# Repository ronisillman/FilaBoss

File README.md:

# FilaBoss
Mechatronics Project Filament Maker

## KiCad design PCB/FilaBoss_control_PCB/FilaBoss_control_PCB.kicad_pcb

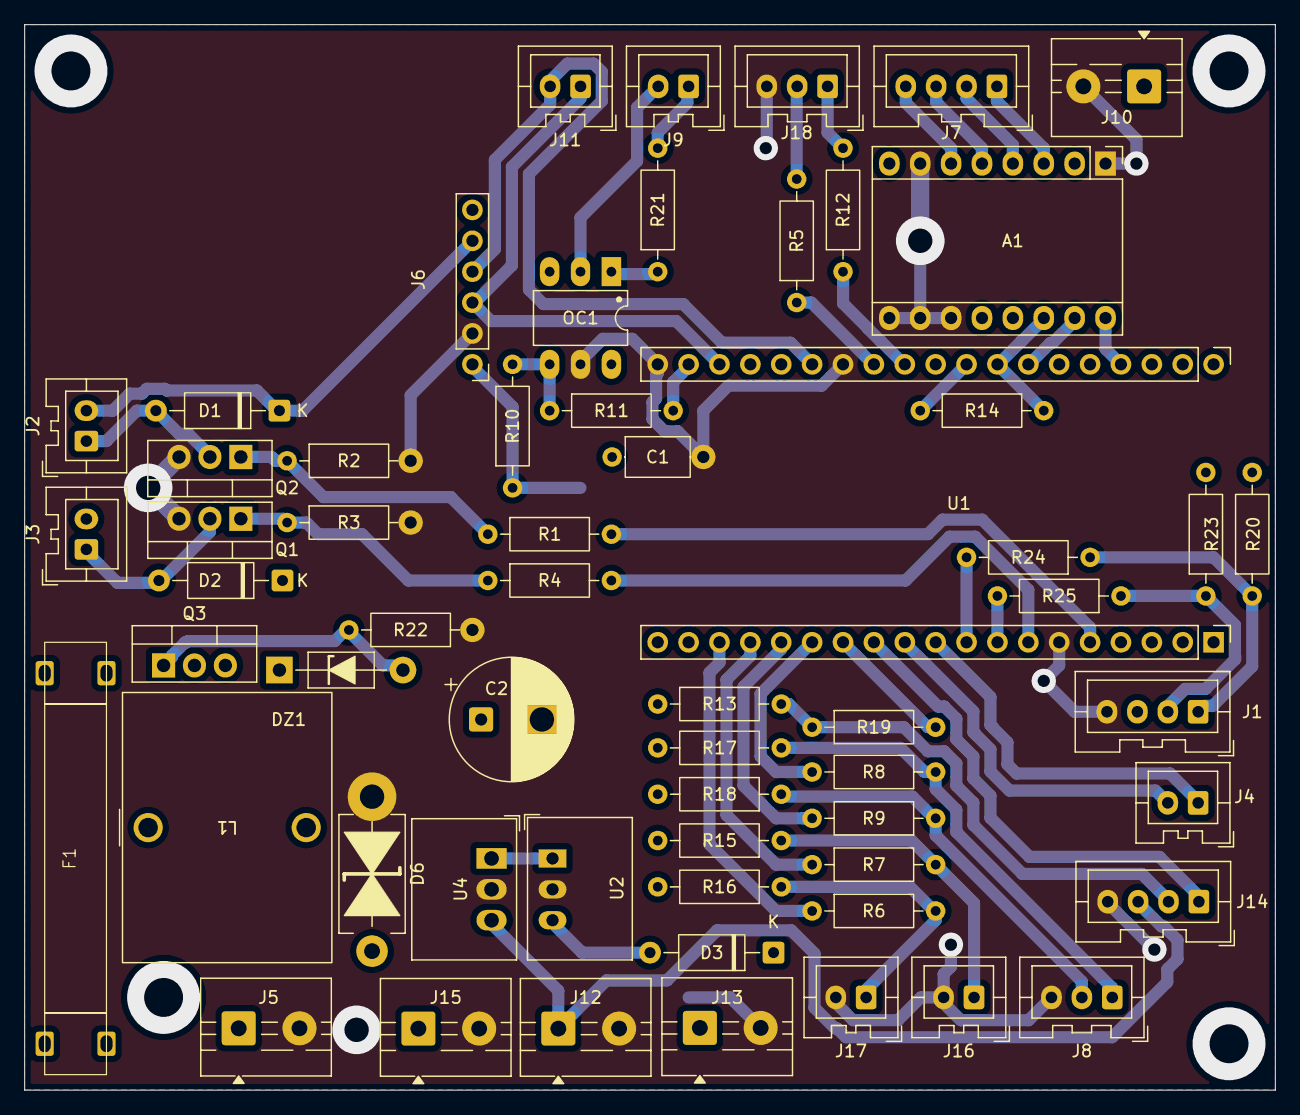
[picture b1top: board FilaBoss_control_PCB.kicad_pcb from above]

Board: 2 copper layers, 102.9 x 87.6 mm, 60 parts (0 on the bottom side), 53 nets.

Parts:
A1: Pololu_Breakout_A4988; Pololu_Breakout-16_15.2x20.3mm
C1: C; C_Axial_L5.1mm_D3.1mm_P7.50mm_Horizontal
C2: C; CP_Radial_D10.0mm_P5.00mm
D1, D2: D; D_A-405_P10.16mm_Horizontal
D3: SB020; D_A-405_P10.16mm_Horizontal
D6: TVS; D_DO-201_P12.70mm_Horizontal_TVS
DZ1: 1EZ15; D_DO-41_SOD81_P10.16mm_Horizontal_Zener
F1: Fuse; fuse
J1: Encoder; JST_XA_B04B-XASK-1_1x04_P2.50mm_Vertical
J2: SPOOL; JST_XA_B02B-XASK-1_1x02_P2.50mm_Vertical
J3: PULLER; JST_XA_B02B-XASK-1_1x02_P2.50mm_Vertical
J4: RX/TX; JST_XA_B02B-XASK-1_1x02_P2.50mm_Vertical
J5: Power; TerminalBlock_MaiXu_MX126-5.0-02P_1x02_P5.00mm
J6: INA219; PinHeader_01x06_P2.54mm_Vertical_THT_D1mm
J7: Stepper; JST_XA_B04B-XASK-1_1x04_P2.50mm_Vertical
J8: limit switch; JST_XA_B03B-XASK-1_1x03_P2.50mm_Vertical
J9: Extruder; JST_XA_B02B-XASK-1_1x02_P2.50mm_Vertical
J10: Power 3.3v; TerminalBlock_MaiXu_MX126-5.0-02P_1x02_P5.00mm
J11: SDA/SCL; JST_XA_B02B-XASK-1_1x02_P2.50mm_Vertical
J12: power 12v; TerminalBlock_MaiXu_MX126-5.0-02P_1x02_P5.00mm
J13: power 5v; TerminalBlock_MaiXu_MX126-5.0-02P_1x02_P5.00mm
J14: Fan connector; JST_XA_B04B-XASK-1_1x04_P2.50mm_Vertical
J15: power 24v; TerminalBlock_MaiXu_MX126-5.0-02P_1x02_P5.00mm
J16: Load; JST_XA_B02B-XASK-1_1x02_P2.50mm_Vertical
J17: manual; JST_XA_B02B-XASK-1_1x02_P2.50mm_Vertical
J18: Control leds; JST_XA_B03B-XASK-1_1x03_P2.50mm_Vertical
L1: L; L_Wurth_WE-HCFT-2012_LeadDiameter1.2mm
OC1: H11A1; DIP-6_W7.62mm_LongPads
Q1, Q2: IRLZ44N; TO-220-3_Vertical
Q3: IRF9540N; TO-220-3_Vertical_GDS
R1, R4: 100R; R_Axial_DIN0207_L6.3mm_D2.5mm_P10.16mm_Horizontal
R2, R3: 10K; R_Axial_DIN0207_L6.3mm_D2.5mm_P10.16mm_Horizontal
R5, R6, R7, R8, R9, R11, R12, R19, R24, R25: 330R; R_Axial_DIN0207_L6.3mm_D2.5mm_P10.16mm_Horizontal
R10, R13, R15, R16, R17, R18, R20, R21, R23: 4.7k; R_Axial_DIN0207_L6.3mm_D2.5mm_P10.16mm_Horizontal
R14: 1K; R_Axial_DIN0207_L6.3mm_D2.5mm_P10.16mm_Horizontal
R22: 2k; R_Axial_DIN0207_L6.3mm_D2.5mm_P10.16mm_Horizontal
U1: ESP32 Wroom dev-kit
U2: R-78E5.0-0.5; Converter_DCDC_RECOM_R-78E-0.5_THT
U4: R-78B12-2.0; Converter_DCDC_RECOM_R-78B-2.0_THT

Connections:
+3.3V: A1.2 (VDD), C1.1, J6.1, J10.1, OC1.6, R10.1, R13.1, R15.2, R16.2, R17.2, R18.2, R20.2, R23.2, U1.19 (3V3)
+5V: D3.1 (K), J1.3, J13.1, U1.1 (5V)
+12V: J12.1, J14.3, U4.3 (OUT)
+24V: A1.8 (VMOT), C2.1, D2.1 (K), D6.2 (A), J3.2, J6.6, J15.1, L1.2, U2.1 (IN), U4.1 (IN)
GND: A1.1 (GND), A1.7 (GND), A1.9 (~ENABLE), A1.10 (MS1), A1.11 (MS2), C1.2, C2.2, D6.1 (K), J1.4, J5.2, J6.2, J8.3, J10.2, J12.2, J13.2, J14.4, J15.2, J16.2, J17.2, J18.3, OC1.5, Q1.3 (S), Q2.3 (S), R2.2, R3.2, R22.1, U1.6 (GND), U1.32 (GND), U1.38 (GND), U2.2 (GND), U4.2 (GND)
LINE: F1.1, J5.1
unnamed: A1.4 (1A), J7.2
unnamed: A1.3 (1B), J7.1
unnamed: A1.5 (2A), J7.3
unnamed: A1.6 (2B), J7.4
unnamed: A1.16 (DIR), U1.23 (GPIO15)
unnamed: A1.15 (STEP), U1.26 (GPIO4)
unnamed: A1.14 (UART), R14.2, U1.27 (GPIO16/RX2)
unnamed: D1.2 (A), J2.1, Q2.2 (D)
unnamed: D1.1 (K), J2.2, J6.5
unnamed: D2.2 (A), J3.1, Q1.2 (D)
unnamed: D3.2 (A), U2.3 (OUT)
unnamed: DZ1.2 (A), Q3.1 (G), R22.2
unnamed: J1.1, R20.1, R24.1
unnamed: J1.2, R23.1, R25.1
unnamed: J4.1, U1.10 (GPIO26)
unnamed: J4.2, U1.11 (GPIO25)
unnamed: J8.1, R8.1, R17.1
unnamed: J8.2, R9.1, R18.1
unnamed: J9.1, R21.2
unnamed: J9.2, OC1.2
unnamed: J6.3, J11.1, U1.36 (GPIO22/SCL)
unnamed: J6.4, J11.2, U1.33 (GPIO21/SDA)
unnamed: J14.1, U1.12 (GPIO33)
unnamed: J14.2, R13.2, R19.1
unnamed: J16.1, R7.2, R15.1
unnamed: J17.1, R6.2, R16.1
unnamed: J18.1, R12.2
unnamed: J18.2, R5.2
unnamed: OC1.1, R21.1
unnamed: OC1.4, R10.2, R11.1
unnamed: Q1.1 (G), R3.1, R4.1
unnamed: Q2.1 (G), R1.1, R2.1
unnamed: R4.2, U1.7 (GPIO12)
unnamed: R1.2, U1.5 (GPIO13)
unnamed: R25.2, U1.8 (GPIO14)
unnamed: R14.1, U1.28 (GPIO17/TX2)
unnamed: R12.1, U1.30 (GPIO18)
unnamed: R5.1, U1.31 (GPIO19)
unnamed: R11.2, U1.37 (GPIO23)
unnamed: R24.2, U1.9 (GPIO27)
unnamed: R19.2, U1.13 (GPIO32)
unnamed: R9.2, U1.15 (GPIO34)
unnamed: R8.2, U1.14 (GPIO35)
unnamed: R6.1, U1.17 (GPIO36)
unnamed: R7.1, U1.16 (GPIO39)
VCC: DZ1.1 (K), L1.1, Q3.3 (S)
VDC: F1.2, Q3.2 (D)

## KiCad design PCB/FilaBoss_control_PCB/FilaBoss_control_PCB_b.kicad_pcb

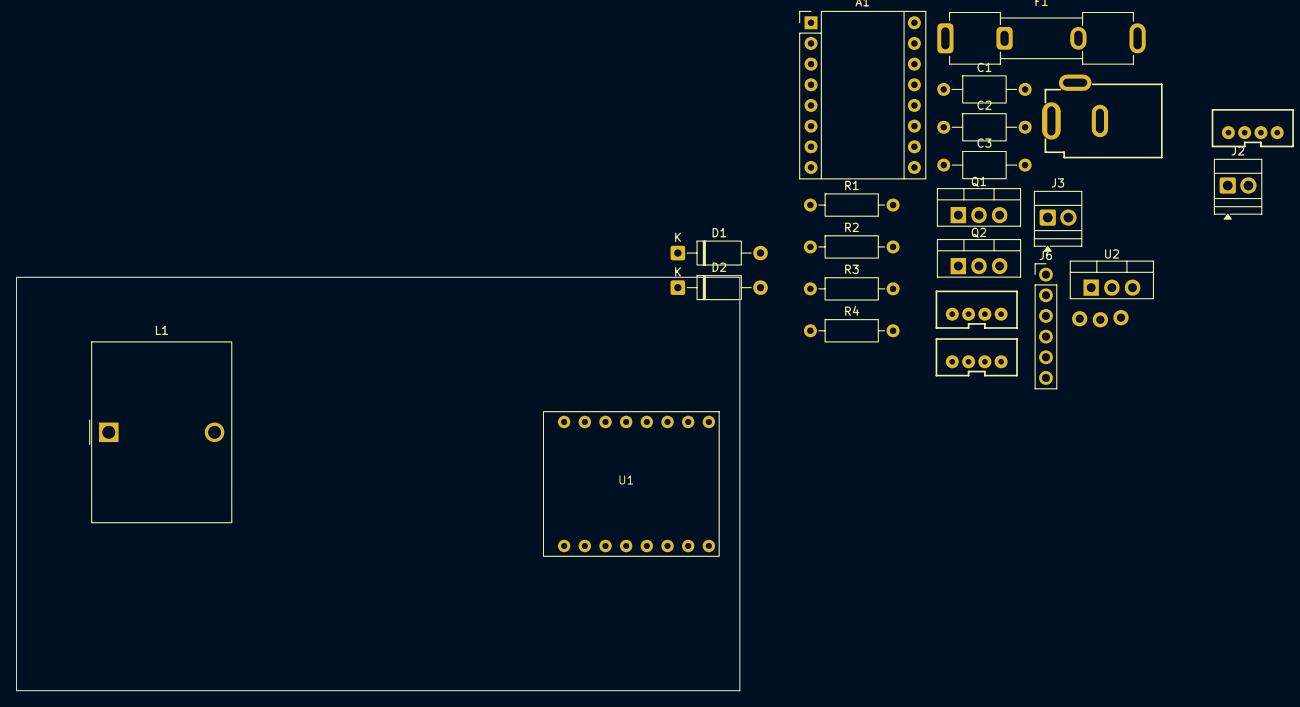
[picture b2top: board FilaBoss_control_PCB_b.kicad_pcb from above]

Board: 2 copper layers, 88.9 x 50.8 mm, 24 parts (0 on the bottom side), 29 nets, no tracks yet.

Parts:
A1: Pololu_Breakout_A4988; Pololu_Breakout-16_15.2x20.3mm
C1, C2, C3: C; C_Axial_L5.1mm_D3.1mm_P10.00mm_Horizontal
D1, D2: D; D_A-405_P10.16mm_Horizontal
F1: Fuse; Fuseholder_Clip-5x20mm_Keystone_3512P_Inline_P23.62x7.27mm_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
J1, J9: Conn_01x04_Encoder; JST_1x04_P2.0mm_Vertical_PTH
J2, J3: Screw_Terminal_01x02; TerminalBlock_Xinya_XY308-2.54-2P_1x02_P2.54mm_Horizontal
J5: Barrel_Jack_PTH_Slot
J6: PinHeader_01x06_P2.54mm_Vertical_THT_D1mm
J7: Conn_01x04; JST_1x04_P2.0mm_Vertical_PTH
J8: Conn_01x03; 1x03_P2.54mm_Locking
L1: L; L_Wurth_WE-HCFT-2012_LeadDiameter1.2mm
Q1, Q2: IRLZ44N; TO-220-3_Vertical
R1, R4: 100R; R_Axial_DIN0207_L6.3mm_D2.5mm_P10.16mm_Horizontal
R2, R3: 10K; R_Axial_DIN0207_L6.3mm_D2.5mm_P10.16mm_Horizontal
U1: ESP32_C3_super_mini; ESP32-super-mini
U2: LM78M05_TO220; TO-220-3_Vertical

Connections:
+24V: F1.1, J5.PWR
GND: A1.1 (GND), A1.7 (GND), A1.9 (~ENABLE), C1.2, C2.2, C3.2, J1.4, J5.GND, J6.2, J8.3, J9.1, Q1.3 (S), Q2.3 (S), R2.2, R3.2, U1.12 (GND), U2.2 (GND)
unnamed: A1.4 (1A), J7.2
unnamed: A1.3 (1B), J7.1
unnamed: A1.5 (2A), J7.3
unnamed: A1.6 (2B), J7.4
unnamed: A1.16 (DIR), U1.20 (D7/RX)
unnamed: A1.2 (VDD), A1.10 (MS1), A1.11 (MS2), A1.12 (MS3), J1.3, J6.1, U1.11 (3V3)
unnamed: A1.15 (STEP), U1.21 (D6/TX)
unnamed: A1.8 (VMOT), C2.1, D1.1 (K), D2.1 (K), J2.1, J3.1, L1.2, U2.1 (VI)
unnamed: A1.13 (~RESET), A1.14 (~SLEEP)
unnamed: D1.2 (A), J2.2, J6.6
unnamed: D2.2 (A), J3.2, Q1.2 (D)
unnamed: F1.2, L1.1
unnamed: J1.1, U1.4 (D2/A2)
unnamed: J1.2, U1.3 (D1/A1)
unnamed: J6.3, U1.7 (D5/SCL)
unnamed: J6.4, U1.6 (D4/SDA)
unnamed: J6.5, Q2.2 (D)
unnamed: J8.1, U1.1 (ADC1-1)
unnamed: J8.2, U1.0 (ADC1-0)
unnamed: J9.2, U1.10 (D10/MOSI)
unnamed: J9.3, U1.9 (D9/MISO)
unnamed: J9.4, U1.8 (D8/SCK)
unnamed: Q1.1 (G), R3.1, R4.1
unnamed: Q2.1 (G), R1.1, R2.1
unnamed: C1.1, C3.1, U1.13 (5V), U2.3 (VO)
unnamed: R4.2, U1.2 (D0/A0)
unnamed: R1.2, U1.5 (D3/A3)

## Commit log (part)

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2026-02-02 arduino code init
2026-02-03 current measurement code init
2026-02-03 measuring two current sensors code
2026-02-03 DC motor control code init
2026-02-03 combining dc motor and current measurement in one code
2026-02-06 Filament guide test file
2026-02-06 Non blocking stepper control(untested)
2026-02-06 Combined arduino control file
2026-02-06 Integration of components
2026-02-06 added encoder code that counts pulses per second
2026-02-08 +pid class
2026-02-08 parallel calibration and homing of the guide stepper
2026-02-09 variable
2026-02-09 variable correction
2026-02-09 added descriptions and fucntions for clarity
2026-02-09 save output in object
2026-02-09 output retrive function
2026-02-09 Ready for testing(configure pin setup and test values)
2026-02-09 bug fix
2026-02-09 encoder implementation and bug fix
2026-02-09 encoder code, deleted motor lines
2026-02-09 fixed encoder code
2026-02-09 9.2.2026 changes
2026-02-09 fixed low pid gain, added filter constants, diagnose function, speed decay
2026-02-18 added pot control for speed for testing
2026-02-18 new code for 600 pulses encoder
2026-02-18 pot controls for both speed and current targets, PID gain for speed and current
2026-02-23 new 24 VDC motors and removal of other current sensor
2026-02-23 removed lqr file
2026-02-23 NEW speed measurment to test, + cleanup
2026-02-23 more cleanup
2026-02-24 corrected pid gains for 24V roller motor
2026-02-24 more smoothing to speed measurement
2026-02-24 int operation, then cast to float
2026-02-24 digital pot. function. NEED more interrupt pins
2026-02-24 prep for board switch
2026-03-02 added stand alone magnetometer measurement code
2026-03-02 added stand alone magnetometer and encoder measurement code
2026-03-04 stepper test
2026-03-04 magnetometer_test update
2026-03-04 added magnetometer measurement to main code
2026-03-04 4.3.2026
2026-03-10 diagnose stepper
2026-03-10 stepper trouble shooting+ interrupt limit switching
2026-03-10 increased baud rate
2026-03-10 10.3
2026-03-10 Optimization, bugfix, stepper diagnostic
2026-03-11 stepper functional
2026-03-13 pcb v1 ready
2026-03-15 forgot custom lib
2026-03-16 bigger esp required
2026-03-16 stepper motor test codes
2026-03-17 pcb converted to esp32 wroom
2026-03-19 pcb-schematic
2026-03-19 full code for esp
2026-03-20 moved everything unnecessary out of interrupt codes
2026-03-24 interrupt -> pcnt, and speed calibration code
2026-03-24 external pullups to encoder
2026-03-25 pcb v2
2026-03-26 pcb documentation
2026-03-27 new pins
2026-03-28 added speed calibration
2026-03-28 distance measurement
2026-03-28 serial input for speed and current
2026-03-28 fan control and rpm measurement
2026-03-28 28.3.2026
2026-03-28 load mode and stepper library
2026-03-28 fixed stepper dir
2026-03-29 tmc uart connection
2026-03-29 load phase: changed to stepper driver
2026-03-31 tmc2209v2 pcb updates
2026-04-01 pcb WIP
2026-04-01 1.4.2026
2026-04-01 changes to setup
2026-04-01 clean up and modifications to load and stepper control
2026-04-01 fixed compile errors
2026-04-01 fixed "#include <Wire.h>" error
2026-04-02 pcb v3
2026-04-02 stepper calibrations
2026-04-02 after reset wait for load mode, added manual mode
2026-04-03 correct fan rpm measurement and fixed extruder srew and manual switch logic
2026-04-03 updated code, only one error situation remains: after reset if control paused is released only after load mode
2026-04-03 fixed distance reset after load mode
2026-04-05 ui display init
2026-04-05 remove .venv from git
2026-04-05 gitignore .venv
2026-04-05 ui modifications
2026-04-05 Remove __pycache__ from repository and gitignore it
2026-04-05 gitignore edit
2026-04-06 blinking motor selection
2026-04-06 test print to ui
2026-04-06 ui encoder test
2026-04-06 reverset encoder directions
2026-04-06 machine vision init
2026-04-06 serial python test init
2026-04-06 serial test modifications
2026-04-06 more simple serial test
2026-04-06 pcb v4
2026-04-06 minimalistic esp serial receive test
2026-04-06 fixed fan speed padding on ui
2026-04-06 ui and simulation updates
2026-04-06 ui simlation display changes
2026-04-06 communication init to esp32 and raspberry main.py
2026-04-07 serial test codes
2026-04-07 esp32 -> rasberry test codes
2026-04-07 send data test
2026-04-07 simultaneous serial test codes
2026-04-07 jsno serial test
2026-04-07 ui shows actual values from esp32
2026-04-07 included the missing current control from ui
2026-04-07 ui default values to same as esp
2026-04-07 faster ui encoder readings
2026-04-07 correct spool current readings to ui
2026-04-07 more fixes to current ui
2026-04-07 correct telemetry reading on ui
2026-04-07 lower stepper run current
2026-04-07 update speed of ui telemetry data to 1 second interval
2026-04-07 added wait screen to ui with esp reset
2026-04-07 increased guide run current
2026-04-08 machine vision
2026-04-08 diameter from machine vision to ui code
2026-04-08 communication socket edits
2026-04-08 v config json
2026-04-08 socket changes
2026-04-08 right socket dir
2026-04-08 socket faster update rate
2026-04-08 logging file includes timestamp and is started on load mode exit
2026-04-08 system services for ui and mv
2026-04-08 added diameter control
2026-04-08 ui seperate pulley gains to esp32
2026-04-08 no unix socket with sim mode ui
2026-04-15 changed "FAN" to "CONTROL"
2026-04-15 fixed exiting load mode
2026-04-15 serial comminucation fix
2026-04-15 saving ui values to config file, and fixed serial comminucation
2026-04-15 new parse fix
2026-04-15 fixed load mode exiting guide bugs
2026-04-15 writing logs to folder instead of usb
2026-04-15 machine vision service to headless
2026-04-15 added gitignores
2026-04-15 machine vision to headless
2026-04-15 system service mv fixes
2026-04-15 camera calibrations
2026-04-15 ui user experience updates, lcd screen simulator match to real screen
2026-04-15 negative pulley diameter gains
2026-04-15 removed config file
2026-04-15 when target 0 -> set speed to 0
2026-04-15 fixed ui pid target values
2026-04-15 ui edits
2026-04-15 more accurate font to ui sim
2026-04-16 better camera calibration codes
2026-04-16 calubration code screen spacing
2026-04-16 changed calibration screen sizes
2026-04-16 removed threshold harcoding from scale calibration
2026-04-16 added missing numpy definition
2026-04-16 launch script for calibration
2026-04-16 better calibration codes
2026-04-16 ui dia measurement to 2 decimals
2026-04-16 target diameter to guide calculations
2026-04-22 cast to int bug fix, pcnt overflow check for speed, lower alpha for speed.
2026-04-22 Cascade dia pid control
2026-04-22 casting fixes
2026-04-22 Millis to micros
2026-04-22 Derivative filtering
2026-04-22 speed measurment timing to micros
2026-04-22 diameter pid changes
2026-04-22 pid derivate changes
2026-04-22 deleted old homing and calibration function
2026-04-22 added N/A sate to UI when no received data
2026-04-22 fixed N/A state
2026-04-22 pid autotune
2026-04-22 comment out json error
2026-04-22 diagnose change
2026-04-27 bugfix
2026-05-05 guide bug fix
